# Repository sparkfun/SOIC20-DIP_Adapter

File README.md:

SOIC20 DIP Adapter
==================

[
*SparkFun SOIC to DIP Adapter 20-Pin (BOB-00495)*](https://www.sparkfun.com/products/495)

This pcb breaks out standard SOIC 20 pin packages to 0.1" headers.

Repository Contents
-------------------
* **/Hardware** - All Eagle design files (.brd, .sch)

License Information
-------------------
The hardware is released under [Creative Commons ShareAlike 4.0 International](https://creativecommons.org/licenses/by-sa/4.0/).
The code is beerware; if you see me (or any other SparkFun employee) at the local, and you've found our code helpful, please buy us a round!

Distributed as-is; no warranty is given.

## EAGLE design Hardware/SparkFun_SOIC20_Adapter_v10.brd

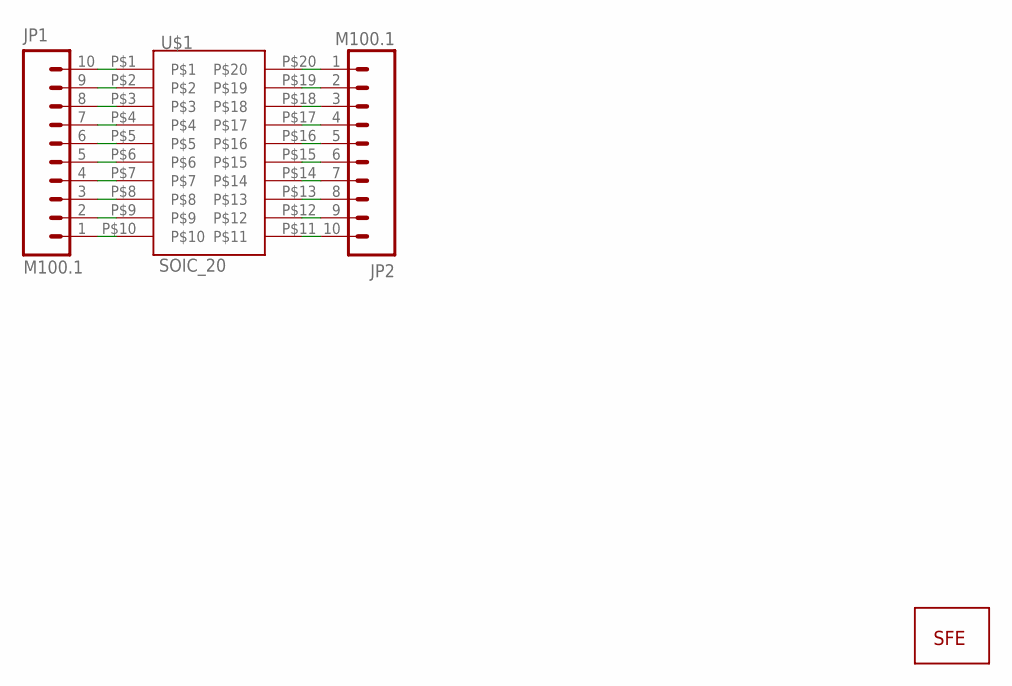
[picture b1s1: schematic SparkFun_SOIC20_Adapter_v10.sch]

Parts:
JP1, JP2: M100.1; 1X10
U$1: SOIC_20; SO20W
U$2: LOGO-SFENEW; SFE-NEW-WEBLOGO

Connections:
unnamed: JP1.1, U$1.P$10
unnamed: JP1.2, U$1.P$9
unnamed: JP1.3, U$1.P$8
unnamed: JP1.4, U$1.P$7
unnamed: JP1.5, U$1.P$6
unnamed: JP1.6, U$1.P$5
unnamed: JP1.7, U$1.P$4
unnamed: JP1.8, U$1.P$3
unnamed: JP1.9, U$1.P$2
unnamed: JP1.10, U$1.P$1
unnamed: JP2.1, U$1.P$20
unnamed: JP2.2, U$1.P$19
unnamed: JP2.3, U$1.P$18
unnamed: JP2.4, U$1.P$17
unnamed: JP2.5, U$1.P$16
unnamed: JP2.6, U$1.P$15
unnamed: JP2.7, U$1.P$14
unnamed: JP2.8, U$1.P$13
unnamed: JP2.9, U$1.P$12
unnamed: JP2.10, U$1.P$11

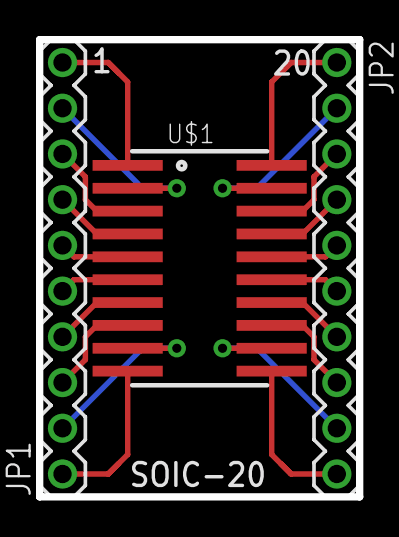
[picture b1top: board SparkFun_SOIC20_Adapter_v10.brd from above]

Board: 2 copper layers, 17.8 x 25.4 mm, 4 parts (1 on the bottom side), 20 nets.

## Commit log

2015-01-06 Initial hardware commit
